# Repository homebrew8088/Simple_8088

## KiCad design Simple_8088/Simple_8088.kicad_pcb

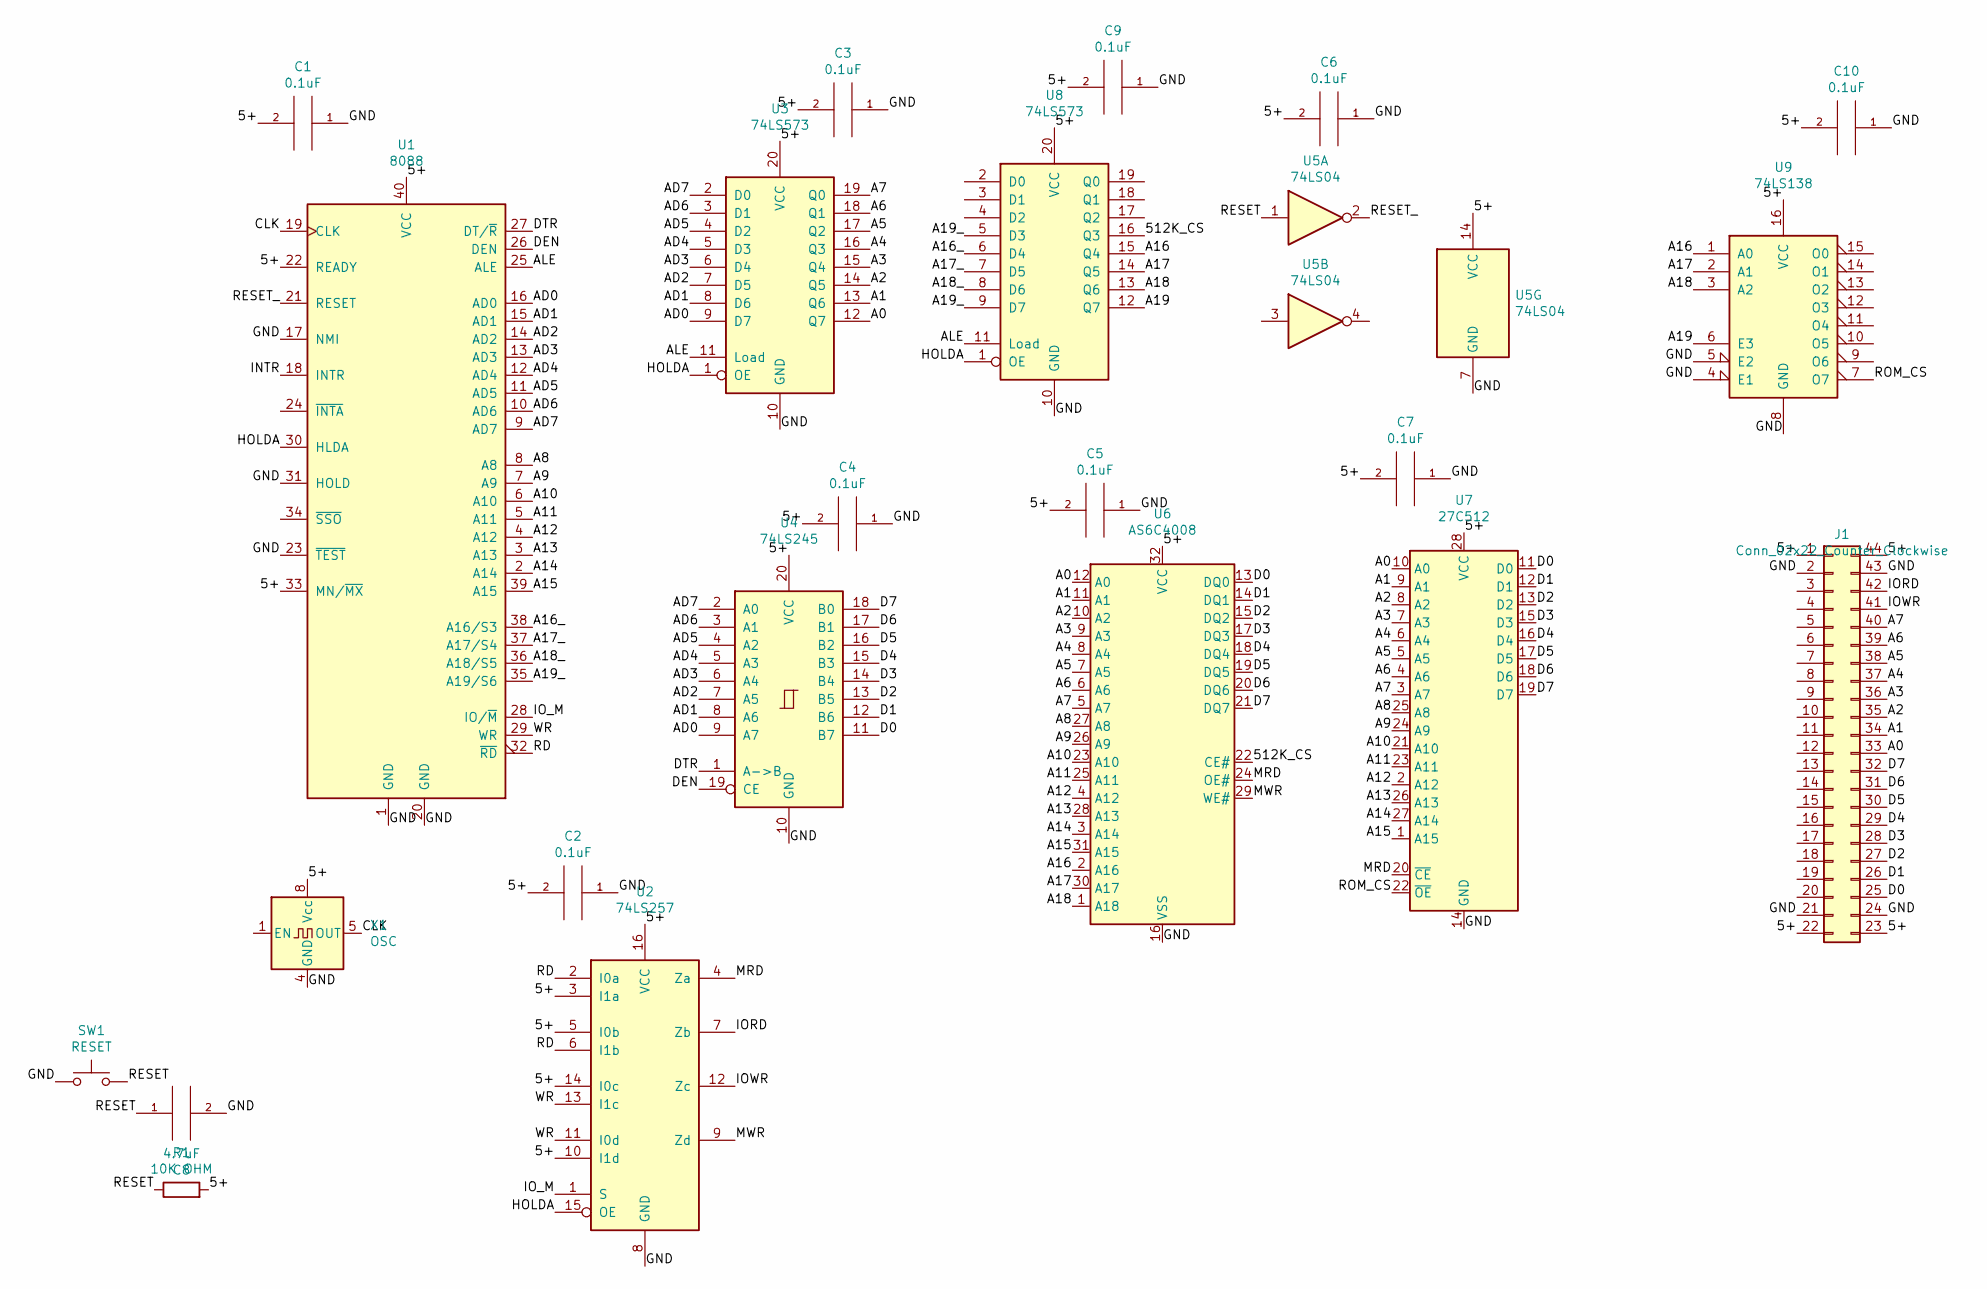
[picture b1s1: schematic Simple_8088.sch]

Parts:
C1, C2, C3, C4, C5, C6, C7, C9, C10: 0.1uF; C_Disc_D4.3mm_W1.9mm_P5.00mm
C8: 4.7uF; CP_Radial_D4.0mm_P1.50mm
J1: Conn_02x22_Counter_Clockwise; 44_EDGE_CARD_BUS
R1: 10K OHM; R_Axial_DIN0207_L6.3mm_D2.5mm_P10.16mm_Horizontal
SW1: RESET; SW_PUSH_6mm
U1: 8088; DIP-40_W15.24mm
U2: 74LS257; DIP-16_W7.62mm
U3, U8: 74LS573; DIP-20_W7.62mm
U4: 74LS245; DIP-20_W7.62mm
U5: 74LS04; DIP-14_W7.62mm
U6: AS6C4008; DIP-32_W15.24mm
U7: 27C512; DIP_Socket-28_W11.9_W12.7_W15.24_W17.78_W18.5_3M_228-1277-0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
U9: 74LS138; DIP-16_W7.62mm
X1: OSC; Oscillator_DIP-8

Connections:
/5+: C1.2, C2.2, C3.2, C4.2, C5.2, C6.2, C7.2, C9.2, C10.2, J1.1, J1.22, J1.23, J1.44, R1.2, U1.22 (READY), U1.33 (MN/~MX~), U1.40 (VCC), U2.3 (I1a), U2.5 (I0b), U2.10 (I1d), U2.14 (I0c), U2.16 (VCC), U3.20 (VCC), U4.20 (VCC), U5.14 (VCC), U6.32 (VCC), U7.28 (VCC), U8.20 (VCC), U9.16 (VCC), X1.8 (Vcc)
/512K_CS: U6.22 (CE#), U8.16 (Q3)
/A0: J1.33, U3.12 (Q7), U6.12 (A0), U7.10 (A0)
/A1: J1.34, U3.13 (Q6), U6.11 (A1), U7.9 (A1)
/A2: J1.35, U3.14 (Q5), U6.10 (A2), U7.8 (A2)
/A3: J1.36, U3.15 (Q4), U6.9 (A3), U7.7 (A3)
/A4: J1.37, U3.16 (Q3), U6.8 (A4), U7.6 (A4)
/A5: J1.38, U3.17 (Q2), U6.7 (A5), U7.5 (A5)
/A6: J1.39, U3.18 (Q1), U6.6 (A6), U7.4 (A6)
/A7: J1.40, U3.19 (Q0), U6.5 (A7), U7.3 (A7)
/A8: U1.8 (A8), U6.27 (A8), U7.25 (A8)
/A9: U1.7 (A9), U6.26 (A9), U7.24 (A9)
/A10: U1.6 (A10), U6.23 (A10), U7.21 (A10)
/A11: U1.5 (A11), U6.25 (A11), U7.23 (A11)
/A12: U1.4 (A12), U6.4 (A12), U7.2 (A12)
/A13: U1.3 (A13), U6.28 (A13), U7.26 (A13)
/A14: U1.2 (A14), U6.3 (A14), U7.27 (A14)
/A15: U1.39 (A15), U6.31 (A15), U7.1 (A15)
/A16: U6.2 (A16), U8.15 (Q4), U9.1 (A0)
/A16_: U1.38 (A16/S3), U8.6 (D4)
/A17: U6.30 (A17), U8.14 (Q5), U9.2 (A1)
/A17_: U1.37 (A17/S4), U8.7 (D5)
/A18: U6.1 (A18), U8.13 (Q6), U9.3 (A2)
/A18_: U1.36 (A18/S5), U8.8 (D6)
/A19: U8.12 (Q7), U9.6 (E3)
/A19_: U1.35 (A19/S6), U8.5 (D3), U8.9 (D7)
/AD0: U1.16 (AD0), U3.9 (D7), U4.9 (A7)
/AD1: U1.15 (AD1), U3.8 (D6), U4.8 (A6)
/AD2: U1.14 (AD2), U3.7 (D5), U4.7 (A5)
/AD3: U1.13 (AD3), U3.6 (D4), U4.6 (A4)
/AD4: U1.12 (AD4), U3.5 (D3), U4.5 (A3)
/AD5: U1.11 (AD5), U3.4 (D2), U4.4 (A2)
/AD6: U1.10 (AD6), U3.3 (D1), U4.3 (A1)
/AD7: U1.9 (AD7), U3.2 (D0), U4.2 (A0)
/ALE: U1.25 (ALE), U3.11 (Load), U8.11 (Load)
/CLK: U1.19 (CLK), X1.5 (OUT)
/D0: J1.25, U4.11 (B7), U6.13 (DQ0), U7.11 (D0)
/D1: J1.26, U4.12 (B6), U6.14 (DQ1), U7.12 (D1)
/D2: J1.27, U4.13 (B5), U6.15 (DQ2), U7.13 (D2)
/D3: J1.28, U4.14 (B4), U6.17 (DQ3), U7.15 (D3)
/D4: J1.29, U4.15 (B3), U6.18 (DQ4), U7.16 (D4)
/D5: J1.30, U4.16 (B2), U6.19 (DQ5), U7.17 (D5)
/D6: J1.31, U4.17 (B1), U6.20 (DQ6), U7.18 (D6)
/D7: J1.32, U4.18 (B0), U6.21 (DQ7), U7.19 (D7)
/DEN: U1.26 (DEN), U4.19 (CE)
/DTR: U1.27 (DT/~R~), U4.1 (A->B)
/GND: C1.1, C2.1, C3.1, C4.1, C5.1, C6.1, C7.1, C8.2, C9.1, C10.1, J1.2, J1.21, J1.24, J1.43, SW1.1, U1.1 (GND), U1.17 (NMI), U1.20 (GND), U1.23 (~TEST~), U1.31 (HOLD), U2.8 (GND), U3.10 (GND), U4.10 (GND), U5.7 (GND), U6.16 (VSS), U7.14 (GND), U8.10 (GND), U9.4 (E1), U9.5 (E2), U9.8 (GND), X1.4 (GND)
/HOLDA: U1.30 (HLDA), U2.15 (OE), U3.1 (OE), U8.1 (OE)
/INTR: U1.18 (INTR)
/IORD: J1.42, U2.7 (Zb)
/IOWR: J1.41, U2.12 (Zc)
/IO_M: U1.28 (IO/~M~), U2.1 (S)
/MRD: U2.4 (Za), U6.24 (OE#), U7.20 (~CE)
/MWR: U2.9 (Zd), U6.29 (WE#)
/RD: U1.32 (~RD~), U2.2 (I0a), U2.6 (I1b)
/RESET: C8.1, R1.1, SW1.2, U5.1
/RESET_: U1.21 (RESET), U5.2
/ROM_CS: U7.22 (~OE), U9.7 (O7)
/WR: U1.29 (WR), U2.11 (I0d), U2.13 (I1c)

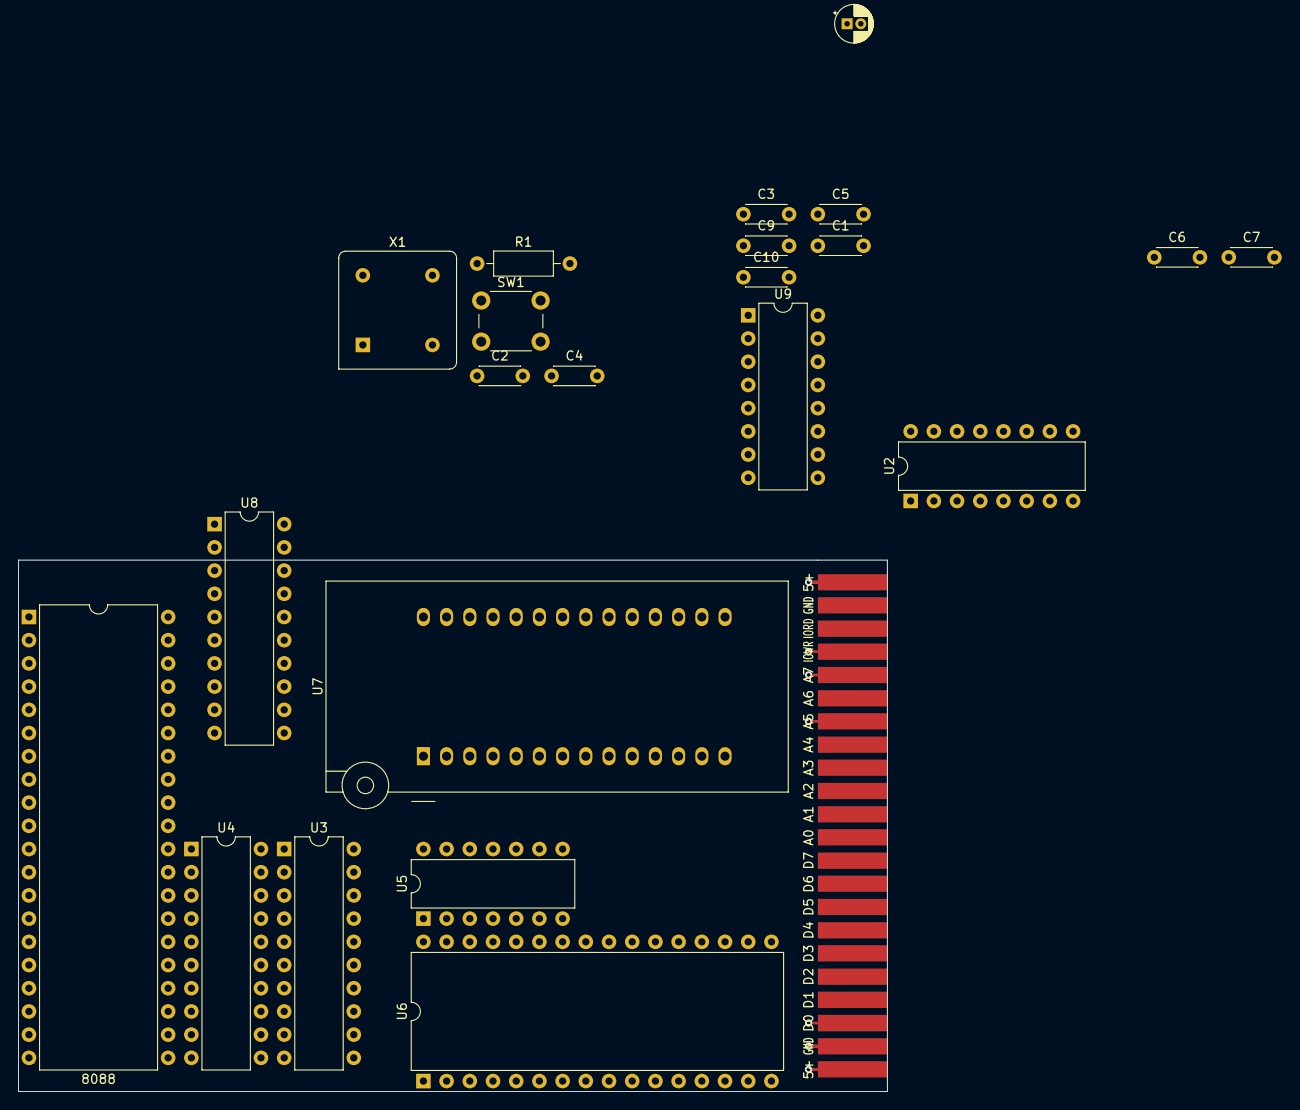
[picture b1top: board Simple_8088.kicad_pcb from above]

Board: 2 copper layers, 95.1 x 58.2 mm, 23 parts (0 on the bottom side), 58 nets.

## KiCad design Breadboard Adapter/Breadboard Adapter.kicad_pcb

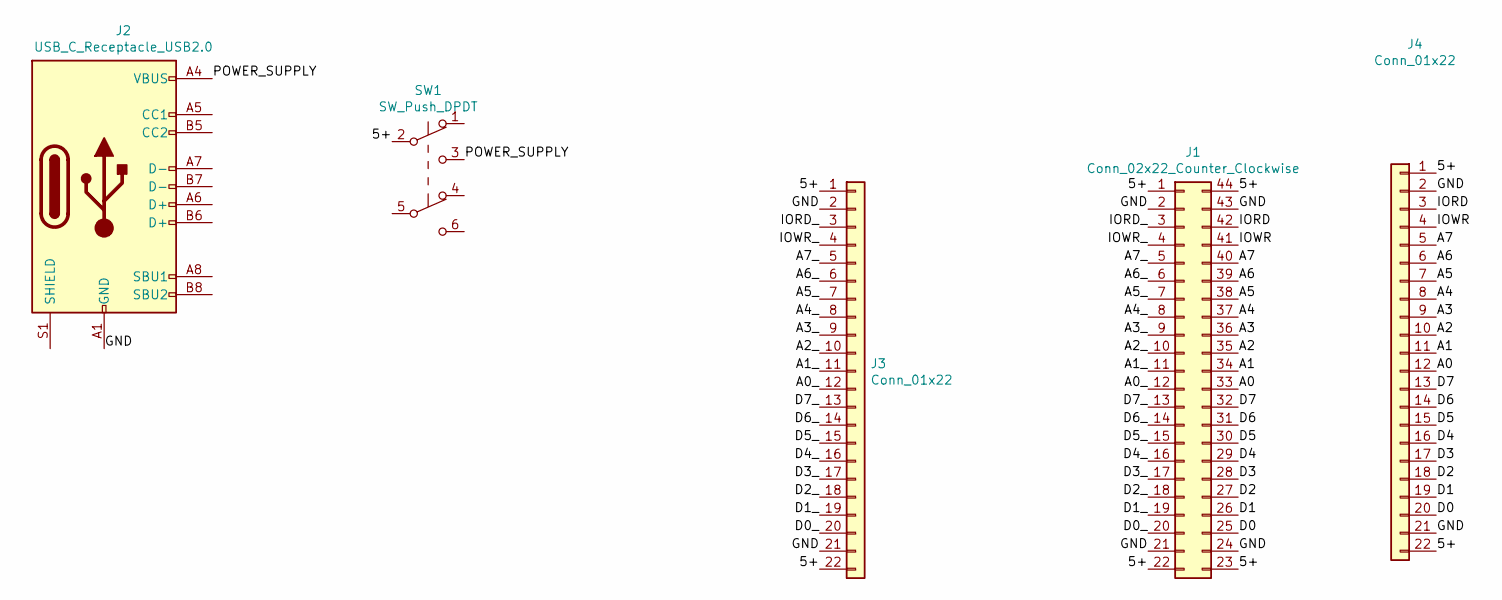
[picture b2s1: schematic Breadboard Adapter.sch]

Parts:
J1: Conn_02x22_Counter_Clockwise; 2x22_PIN_EDGE_CARD
J2: USB_C_Receptacle_USB2.0; USB_C_Receptacle_GCT_USB4085
J3, J4: Conn_01x22; PinHeader_1x22_P2.54mm_Vertical
SW1: SW_Push_DPDT; 6 PIN DTDP

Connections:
/5+: J1.1, J1.22, J1.23, J1.44, J3.1, J3.22, J4.1, J4.22, SW1.2 (B)
/A0: J1.33, J4.12
/A0_: J1.12, J3.12
/A1: J1.34, J4.11
/A1_: J1.11, J3.11
/A2: J1.35, J4.10
/A2_: J1.10, J3.10
/A3: J1.36, J4.9
/A3_: J1.9, J3.9
/A4: J1.37, J4.8
/A4_: J1.8, J3.8
/A5: J1.38, J4.7
/A5_: J1.7, J3.7
/A6: J1.39, J4.6
/A6_: J1.6, J3.6
/A7: J1.40, J4.5
/A7_: J1.5, J3.5
/D0: J1.25, J4.20
/D0_: J1.20, J3.20
/D1: J1.26, J4.19
/D1_: J1.19, J3.19
/D2: J1.27, J4.18
/D2_: J1.18, J3.18
/D3: J1.28, J4.17
/D3_: J1.17, J3.17
/D4: J1.29, J4.16
/D4_: J1.16, J3.16
/D5: J1.30, J4.15
/D5_: J1.15, J3.15
/D6: J1.31, J4.14
/D6_: J1.14, J3.14
/D7: J1.32, J4.13
/D7_: J1.13, J3.13
/GND: J1.2, J1.21, J1.24, J1.43, J2.A1 (GND), J2.A12 (GND), J2.B1 (GND), J2.B12 (GND), J3.2, J3.21, J4.2, J4.21
/IORD: J1.42, J4.3
/IORD_: J1.3, J3.3
/IOWR: J1.41, J4.4
/IOWR_: J1.4, J3.4
/POWER_SUPPLY: J2.A4 (VBUS), J2.A9 (VBUS), J2.B4 (VBUS), J2.B9 (VBUS), SW1.3 (C)

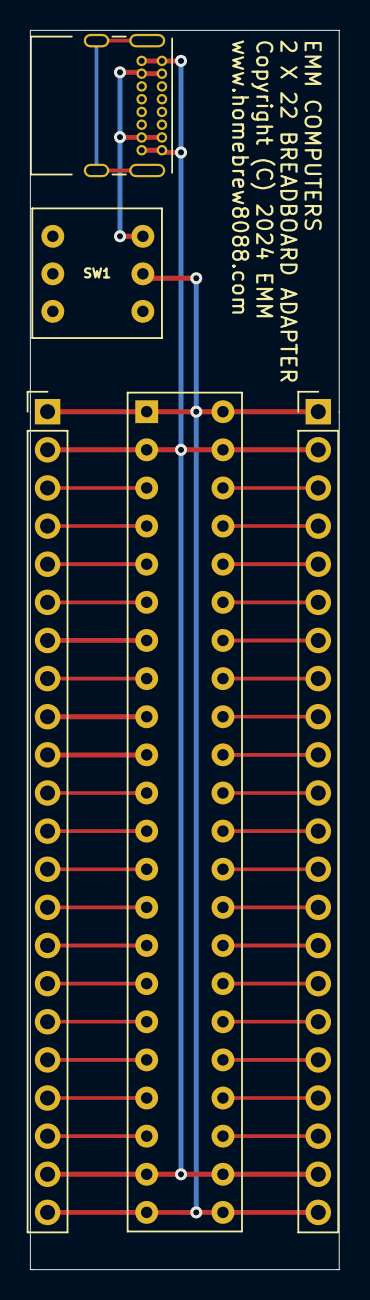
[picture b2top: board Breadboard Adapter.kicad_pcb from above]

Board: 2 copper layers, 20.6 x 82.5 mm, 5 parts (0 on the bottom side), 39 nets.

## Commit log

2024-04-11 Created
2024-05-01 Changing RAM

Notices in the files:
Breadboard Adapter/Breadboard Adapter.kicad_pcb:
Copyright (C) 2024 EMM
